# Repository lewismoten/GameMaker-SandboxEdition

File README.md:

# Game-Maker: Sandbox Edition

![Game-Maker: Sandbox Edition. Make 1994 DOS games. No programming. A painted 1994 desk at night by a snowy window: the beige PC shows DOS Game-Maker's Map Maker menu, with a sticky note reading "Too retro? Use today's web" pointing to a tablet showing the site's home page, and around it sit a disk box, TURBO BUTTON magazine, the keyboard, a mug of pencils and the Game-Maker box](docs/social-preview-600x300.png)

Make and play DOS-style games in your web browser, with no programming. A modified fork of
**RSD Game-Maker 3.0**, the 1991–1995 game construction kit by Recreational Software
Designs, whose source Andy Stone released under the MIT License in 2014.

**▶ Play it: https://lewismoten.github.io/GameMaker-SandboxEdition/**

**Videos:** [RSD Game Maker - Sandbox Edition](https://www.youtube.com/watch?v=0riemzdF8gc), a
tour of the web port, the editor and the 1994 desk, and
[More Features](https://www.youtube.com/watch?v=gNEya63wDmo), what has been added since. Both
are in the site's Library too.

This fork is kept by Lewis Moten, who shoveled Fort Ashby's driveways in the winter of 1992
to buy Game-Maker. The desk, the BBSes and _Snowbound_ come from those years: see
[Lewis and Game-Maker](docs/history.md).

## What's in it

- **Three ways to use it** (the Desk, DOS and Web switch at the top right): the _1994 desk_,
  a recreated PC with a DOS prompt, Game-Maker's DOS menus and designers rebuilt from its
  source, a BBS to dial, and the games' boxes, disks and manuals on the shelf; _DOS_, the
  same PC's screen on its own, filling the window without the desk around it; or _today's
  web_ editor with point-and-click editors for every part of a game.
- **Help making good games:** the map editor's Level check plays each scene on the real
  engine, draws a heat map of where the hero got, marks places a player can get stuck and
  offers one-click fixes; the block, monster and sound editors show its findings as badges,
  a Before You Upload checklist ticks itself, and a bot can make a walkthrough of your game.
  The Game-Maker box holds _The Ultimate Owner's Guide_, an advanced booklet on level design,
  tricks from the new games and these tools.
- **A port, not a PC emulator:** Game-Maker and its PLAYGAME player are re-implemented in
  TypeScript from the released C source, and no DOS or x86 code runs. The desk's PC is a
  simulation; some hardware is emulated (VGA mode 13h, the OPL2 FM sound chip).
- **Original file formats:** games are read and written byte for byte as `.GAM`, `.MAP`,
  `.BBL`, `.MON`, `.CHR`, `.CMF`, `.FLI` and the rest, so a game made here still runs in DOS
  Game-Maker and DOSBox, and old games open here unchanged.
- **Byte-identical, checked:** the same code makes the same bytes. `npm run check:games`
  builds each new game twice into separate folders and fails if any file differs;
  `npm run roundtrip` reads every original file, writes it back and compares the bytes;
  `npm run check:same-bytes` hashes every built game file before and after a refactor and
  lists what changed. A refactor must not change a generated byte.
- **The CD's games:** the sample "gameware" (edit a copy) and the shareware (play only,
  with their authors' notices). CD games that shipped without a title demo get one recorded
  for this edition, kept apart from their original files.
- **Fourteen new Sandbox Software games** built for this fork, entirely in code
  ([games/](games)): _Maximus: The Hundred Worlds_, _Sandcastle Knight_, _Snowbound: The $89
  Shovel_, _In The Year 2000!_, _Teddy's Little Big Adventure_, _Teddy's Little Bigger
  Adventure_, _Teddy's Little Biggest Adventure_, _Ohm Sweet Ohm_, _Virus Blaster_, _Final
  Curtain_, _KEEP IT BRIEF! The Tiny Pockets Library_, _Depth Perception_, _Quest for the
  Round Tuit_ and _Tune-Up_. Each comes
  with a manual, box art, printable extras (among them a fold-out World Map and Level Maps)
  and a hidden tin heart, and most hide a felt egg to find.
- **Twelve "bizarre" games**, also built in code from Lewis's own comic songs and
  monologues, dressed as 1995 shareware from The Sofa BBS: eleven by The Bard of Bizarre
  (_Third Goat from the Left_, _Mustard Seed Hustle_, _Thread the Needle, Brother Camel_,
  _Loaf #13_, _Certified Rat Tickler_, _Where's the Remote?!_, _A Fly Named Carl_, _The Great
  Dairy Reckoning of 3:17 A.M._, _Cleanse Me, O Loofah, But Leave My Soul_, _I Screamed, She
  Smirked_ and _Shakespeare in Sweatpants_) and _Veni, Vidi, Risi!_ by Lewis's group of that
  name. They have a Bizarre tab of their own on the home page. Their FM music is arranged
  from the songs' recordings, and they are free to share.
- **The cast** ([#/cast](https://lewismoten.github.io/GameMaker-SandboxEdition/#/cast)):
  the characters who turn up in more than one of the new games, walking on with their own
  game sprites.
- **Demos and walkthroughs:** title demos play with Sound Blaster music, the PC speaker or
  no sound, and every new game has a walkthrough that plays it from power-on to the
  credits on the real engine, with chapters, ready to download as an MP4.
- **The desk PC's utilities:** HEXEDIT, BACKUP, SAVEHACK and GMCRACK, in 1990s dress but
  mainly for looking inside game files, saved games and registration while debugging.
- **The BBSes:** a modem with a line speed to pick (300 baud to unlimited), a tic-tac-toe
  door game played a move a call, and a TTY call to the neighbor in Baudot.
- **Achievements** for what you make, play and find, on the web and in the desk's ACHIEVE.EXE,
  and two score trophies on the desk (best scores and total score) that climb from plastic
  through bronze, silver and gold.
- **The Library** ([#/library](https://lewismoten.github.io/GameMaker-SandboxEdition/#/library)):
  everything to read or print in one place, by game or by kind: each game's manual and box
  paper, its World Map and Level Maps, the Game-Maker box's Owner's Guide, the walkthroughs and
  the videos.
- **Sharing:** export a game as a one-page web game, an installable web app, or a folder
  that runs in DOSBox, or download any game, your own too, as a Mac app, a Windows program
  or a Linux folder that plays offline in its own window (built in the browser; see the
  [Mac](mac/README.md), [Windows](win/README.md) and [Linux](linux/README.md) notes).
  Everything is saved in your browser and works offline.
- **Opening games from other sites:** a link (`?open=<address of the game>`) or a page using
  `window.open` and `postMessage` can open a game here to play or edit, on the desk, in DOS
  Game-Maker or on the web, after the visitor says yes. See
  [Opening games from your site](docs/embed.md).
- **A web player for your old games:** one `.html` file to put on any web host beside your
  Game-Maker game folders. It lists them from an optional `games.json`, starts one from
  `?game=<name>`, and keeps high scores and saved games in the browser, with export and
  import. [Try it with the games here](https://lewismoten.github.io/GameMaker-SandboxEdition/player/)
  or see [The web player](docs/web-player.md).
- **Reusable npm packages:** run Game-Maker DOS files in your own web application with the
  browser engine, build or check game data with the development tools, and load game archives. See
  [npm packages](#npm-packages) for installation and API documentation.

## Screenshots

|                                                                                                                                                                                                                                             |                                                                                                                                                                                                                        |
| ------------------------------------------------------------------------------------------------------------------------------------------------------------------------------------------------------------------------------------------- | ---------------------------------------------------------------------------------------------------------------------------------------------------------------------------------------------------------------------- |
|                                                                                |                                 |
| The home page's Sandbox games                                                                                                                                                                                                               | Editing a copy of Snowbound's LaVale Mall map                                                                                                                                                                          |
|                                                                                             |                                                                             |
| Playing Snowbound                                                                                                                                                                                                                           | The Bizarre games                                                                                                                                                                                                      |
|  |  |
| Game-Maker's DOS menus, rebuilt from its source                                                                                                                                                                                             | Its copy check, with the Owner's Guide beside it                                                                                                                                                                       |

[A tour of the web editor](docs/editor.md) has a picture of each of its editors: maps, blocks,
monsters, the hero, palettes, music, sounds, animations, the Integrator, the Level check and more.

## npm packages

Use these packages in a separate JavaScript or TypeScript project, installed from your
configured npm registry. All include TypeScript declarations.

**[@lewismoten/gamemaker-sandbox-engine](web/packages/engine/README.md)** runs games from
their original DOS files in a browser and includes the audio worklet. Its README provides
the API, a complete player example, and instructions for supplying game files.

```sh
npm install @lewismoten/gamemaker-sandbox-engine
```

**[@lewismoten/gamemaker-sandbox-tools](web/packages/tools/README.md)** provides development
APIs for reading and writing game formats, drawing indexed artwork and text, building
palettes and audio, and running headless checks. Its README documents the APIs and examples.
Use Node.js 22.12 or newer for these tools.

```sh
npm install --save-dev @lewismoten/gamemaker-sandbox-tools
```

The tools run during development; browser playback uses the engine and generated game data.

**[@lewismoten/gamemaker-sandbox-archives](web/packages/archives/README.md)** discovers games
in folders, ZIPs, nested archives, and ZIP-based self-extracting executables. It can also
create ZIPs for single-file downloads. Its README covers extraction, game selection, and
passing the unpacked file entries to the browser engine.

```sh
npm install @lewismoten/gamemaker-sandbox-archives
```

## Run it yourself

You need [Node.js](https://nodejs.org/) 22.12 or later.

```sh
npm ci             # from the repository root; builds workspace packages and game output
npm run dev        # http://localhost:5173
npm run dev -- -- --port 4174  # use another port; the second -- forwards flags to Vite
npm test           # the test suite (vitest)
npm run typecheck  # tsc --noEmit
npm run build      # refresh game output, typecheck, then the static site in web/dist
npm run format     # Prettier (config at the repo root)
npm run lint       # ESLint
npm run verify:changed  # quick pre-merge check of only what your branch touched (vs origin/develop; --base <ref>)
npm run verify     # the full check: format, lint, typecheck, every test, packages, release notes
```

This is an npm workspace monorepo with one root lockfile. The root `package.json` exists to declare
the workspaces (`web` and `web/packages/*`) so a single `npm ci` links them and one
`package-lock.json` pins everything; `npm start` there runs the web dev server. The app is in `web/`;
self-contained engine, archives and tools packages own their source in `web/packages/`.
See [workspace development](docs/monorepo.md) for package ownership, isolated builds and release checks.

The repository was reformatted with Prettier in a few big commits. They are listed in
[`.git-blame-ignore-revs`](.git-blame-ignore-revs), which GitHub's blame view already skips.
To make `git blame` on your own computer skip them too, run this once in your clone:

```sh
git config blame.ignoreRevsFile .git-blame-ignore-revs
```

The new games are rebuilt from their code, also from `web/`:

```sh
npx vite-node ../games/teddy/build.ts             # rebuild games/teddy/disk
npx vite-node ../games/teddy/tools/check.ts       # play-test it headlessly
npx vite-node scripts/macDmg.ts teddy             # a Mac .dmg of it, in ../dist/mac
npx vite-node scripts/winExe.ts teddy             # a Windows .exe, in ../dist/win
npx vite-node scripts/linuxTar.ts teddy           # a Linux .tar.gz, in ../dist/linux
```

To check every game at once (each one rebuilt and compared with its committed disk, played
by its bot, its walkthrough replayed, its text, hidden items and levels checked), run
`npm run check:games` from `web/`. It prints a table and fails on any regression; add
`-- --game teddy` for one game or `-- --quick` to skip the rebuild compare.

The site is served by GitHub Pages from the `gh-pages` branch: one commit holding the built site of a
`pages-v*` release tag, made on the maintainer's computer by `npm run release:pages` (see
[package releases](docs/package-releases.md#publishing-the-site-gh-pages)). Branch pushes do not publish the site.
The `mac-dmg`, `win-exe` and
`linux-tar` workflows build every game for each system and attach them to a GitHub release.
Engine, tool, and archive releases are described in [Package releases](docs/package-releases.md).
Games are deployed as standalone DOS ZIPs with [permanent download links](docs/game-distributions.md),
shared by the browser player, editor and DOS downloads.
Every GitHub job stops after five minutes, including deployments and release builds.
Checking every game takes far longer than that, so run `npm run check:games` (with the rebuild
compare, about 20 minutes) yourself before committing a game.
Run whole-game checks locally with `npm run check:games` from `web/` (or add
`-- --game <id>` for one game). GitHub jobs are capped at five minutes; tests over
50 ms and isolated package-consumer checks run locally.

## Where things are

| Folder                                          | What it holds                                                                                                                                                                                                                                                                                                                                                                                                                                       |
| ----------------------------------------------- | --------------------------------------------------------------------------------------------------------------------------------------------------------------------------------------------------------------------------------------------------------------------------------------------------------------------------------------------------------------------------------------------------------------------------------------------------- |
| [`web/`](web)                                   | The browser app. [web/README.md](web/README.md) explains it; [web/src/README.md](web/src/README.md) maps the source.                                                                                                                                                                                                                                                                                                                                |
| [`games/`](games)                               | The Sandbox Software and Bard of Bizarre games, built in code, and the shared kit that builds and play-tests them. See [games/README.md](games/README.md) and [games/kit/README.md](games/kit/README.md).                                                                                                                                                                                                                                           |
| [`docs/`](docs)                                 | [A tour of the web editor](docs/editor.md); for site owners, [opening a game from your own site](docs/embed.md) and [the web player](docs/web-player.md); and [Lewis and Game-Maker](docs/history.md), how the project came about; [how I built this](docs/agents/how-i-built-this.md) and [working with AI coding agents](docs/agents/README.md), what building it that way taught; and [case studies](docs/research/README.md) of measured fixes. |
| [`mac/`](mac), [`win/`](win), [`linux/`](linux) | The small native players that a downloaded game runs in, and how they are built. See [mac/README.md](mac/README.md), [win/README.md](win/README.md) and [linux/README.md](linux/README.md).                                                                                                                                                                                                                                                         |
| `cd/`                                           | The original Game-Maker CD image, with its sample and shareware games.                                                                                                                                                                                                                                                                                                                                                                              |
| [`code/`](code)                                 | The original DOS C/C++ source. See [code/README.md](code/README.md).                                                                                                                                                                                                                                                                                                                                                                                |
| `runtime/`                                      | A DOS `C:` drive with Game-Maker installed, for DOSBox.                                                                                                                                                                                                                                                                                                                                                                                             |

## The original DOS version

To run the original Game-Maker, install [DOSBox](https://www.dosbox.com/), start it from
the root of this repository, and type:

```
mount c runtime
c:
cd \run\gm
gm
```

To build the DOS source you also need the Borland C++ compiler, which this fork doesn't
include, nor the Borland and Creative library files it links (none are covered by the
MIT License; NOTICE.md lists them). Copy the `tools/` folder and those files from the
[original 2014 repository](https://github.com/gandrewstone/GameMaker) into this one, then,
following Andy Stone's original notes, in DOSBox:

```
c:
dev.bat          (mounts the compiler as T: and the source as D:)
d:
cd gm
del *.obj
del *.exe
creatall         (or "create palchos", "create blocedit"… for one program)
```

## Learn more

- [CONTRIBUTING.md](CONTRIBUTING.md): branches, checks, release notes and credits
- [Game-Maker on Wikipedia](https://en.wikipedia.org/wiki/Game-Maker)
- ["RSD GameMaker"](https://effluviaofascatteredmind.blogspot.com/2011/06/rsd-gamemaker.html),
  Andy Stone looking back on it in 2011: building it as a teenager with his family, and
  leaving every game open in the editors so players could learn from and remix each other's work
- [The Game-Maker wiki (archived)](https://web.archive.org/web/20260807223841/https://aderack.com/game-maker/index.php?title=Main_Page)
- [The original 2014 source release](https://github.com/gandrewstone/GameMaker)

## Credits and license

RSD Game-Maker was created by G. Andrew Stone, G. Oliver Stone, Oliver Stone Jr. and Joan
Stone. This fork is by Lewis Moten; the web port was written with Claude Opus 5.5, with AI
assistance doing most of the porting and code generation. The Bard of Bizarre songs'
lyrics were shaped with ChatGPT from Lewis's prompts and their music made with Riffusion
(now Google Flow Music). The CD's games belong to their authors, as shareware or samples distributed on the RSD CD, and are not covered by the MIT License; neither are games you import. See [NOTICE.md](NOTICE.md)
for full credits, the story behind this fork and third-party trademarks.

Released under the [MIT License](LICENSE). It covers the original source Andy Stone released and this fork's own code and content; third-party material and other authors' games keep their own terms (NOTICE.md lists them).

The [native SDL host prototype](hardware/pi-player/README.md) compiles the [Pocket Player](https://github.com/lewismoten/gamemaker-pocket) core (its own repository) for macOS and prepares the Raspberry Pi OS Lite player.

The [courier C99 wire library](hardware/courier/README.md) provides self-checking courier IDs and the capsule v1 codec for hardware integrations.

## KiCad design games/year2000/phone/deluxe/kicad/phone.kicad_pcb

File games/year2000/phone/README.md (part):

# THE PHONE OF THE FUTURE (electronics, rev C)

A solderable toy kit that goes with In The Year 2000!: "a real working wireless phone", the way a 1993 game
imagined one. Infrared voice and touch tones, an eight-digit red display, a real pulse dial, a PIC16F628A and a
CM8870-family tone decoder, through-hole parts only. Two phones are needed to play: digits dialed on one appear on any
phone in sight (no call set-up).

**This is an untested design. Nobody has built one. Treat every claim below as "should", not "does".**
The schematic and board pass KiCad's electrical and design-rule checks and the firmware's logic passes a simulator
I wrote; nothing was powered, soldered or listened to.

Rev C is the cheap, easy-to-build revision. Rev B cost about $68 a phone in parts (most of it a $24 display driver), needed a
72 x 172 mm board (about $96 for three from OSH Park) and a programmer that may not support its chip. Rev C is about $17 a phone in
parts, a 99 x 99 mm board in the cheapest tier at JLCPCB and PCBWay, and a programmer built from an Arduino Nano. The numbers and
sources are in the cost sheet (`.for-lewis/research/phone-of-the-future-parts.md`, not in the repository); the short version is
in "What Rev C changed" below.

## Two builds, named the way Dex would

Dex Dynamo (age 11) wrote a twenty-page science fair report, THE POCKET TELEPHONE, and Sparky 3000 ate it. This kit is
what he would build from it, in two sizes. Both names are on the silkscreen (front and back) and in the desk's 3D viewer.

|       | **Science Project No. 2: The Pocket Telephone, Junior Lab Edition (parts from any hobby shop)**                                                                 | **Science Project No. 1: The Pocket Telephone (Deluxe Model)**                                                |
| ----- | --------------------------------------------------------------------------------------------------------------------------------------------------------------- | ------------------------------------------------------------------------------------------------------------- |
| Where | this folder                                                                                                                                                     | `deluxe/` (the earlier Rev C: sources restored from commit `7e8548a11`, see `deluxe/README-earlier-rev-c.md`) |
| Board | 99 x 99 mm, the cheapest board tier                                                                                                                             | 73.66 x 175.26 mm                                                                                             |
| Parts | PIC16F628A, clone MAX7219, 6 mm tactile switches, ZEPPP programmer; the battery holder and the microphone capsule are off the board, in the shell's battery bay | the long board; the 4 x AAA holder and the microphone are in the bay                                          |
| Shell | one full-width case: earpiece pod, front cover, back tray with the battery bay behind the dial module, battery door, six screws                                 | front cover, back tray with the bay (battery door in its floor)                                               |

Each folder rebuilds on its own (`deluxe/tools/` has its own generators and shares `tools/silkart.py` and `tools/dex_art.py`).
The rest of this file describes the Junior Lab Edition; the Deluxe Model differs in its board and its on-board battery holder.

## The 3D-printed shell and the dial module

`tools/shell.ts` builds each variant's shell as distance fields with the repository's trinket tools (`web/packages/tools/src/mesh/`), sized from its own
`mechanical/interface.json`, `kicad/qr_spots.json` and `viewer/parts.json`. It writes one binary STL per printed part, in printing orientation, to
`<variant>/shell/`, checks each (size, triangles, pieces, thin specks, overhang) and merges every part into `viewer/parts.json` + `parts.bin`, in the
groups `shell`, `dial` and `battery`, so the desk's viewer explodes the case around the board. The Junior Lab case is `tools/shellCheap.ts` (with the dial in
`tools/dialModule.ts`); the Deluxe keeps its own shell in `tools/shellParts.ts`, which is described in `deluxe/README-earlier-rev-c.md`.

### The Junior Lab case: one full-width body

The case is 103.8 mm wide from the top to the chin (the board is 99 x 99) and about 240 mm long, 34 mm thick. Seen from the front, top to bottom:

1. **Earpiece pod** (above the board, between the two infrared parts): the 28 mm speaker clips under the cover's roof, behind a grille of 2 mm holes. Two
   2 mm arms per clip follow the speaker's rim and end in a barb (an 0.8 mm ledge under its back rim), so the speaker snaps in from the back and nothing is glued.
   Two wires (+ is the square pad) run from the board's LS1 pads. This frees the 28 mm circle the speaker used on the board (616 mm2; the pads stay).
2. **The 99 x 99 board**, clamped between the cover's and the tray's walls by the corner bosses.
3. **Lower body**: the dial module sits in the cover (its plate stands 0.8 mm proud of the face), the 4 x AAA holder lies behind it in the tray (the module's base
   lies 0.2 mm over the holder like a lid), the microphone capsule is at the chin under a grille.

_Why this layout._ The dial is below the board where a thumb or finger reaches it best, with room for a 74 mm plate and 13 mm holes. The heaviest part, the
battery, is directly behind the dial, so the phone's weight sits in the palm of the hand that holds the lower body, the thumb reaches the TALK and CLEAR caps
on the board's lower edge, the earpiece is at the top and the mouthpiece at the bottom, 190 mm apart, about a real handset's span. The back is flat and closed.

- **Front cover**: covers everything except the dial opening (a 76.4 mm hole), the display window, the speaker and mouthpiece grilles and the TALK / CLEAR
  caps. The dial module's tube hangs from the roof around the opening; the base's rim seats against its end, so nothing is glued. The finger stop's clip
  comes through a small slot at 4 o'clock. It prints face down.
- **Back tray**: closed, one flat floor 20.7 mm under the board's back plane (a stepped floor would print as an 11,000 mm2 overhang). The battery cradle has crush
  ribs 0.3 mm off the holder on all four sides; the door is in the floor under the holder, so the cells change **without opening the case**. The volume wheel's
  slot is in the side wall. Six screw seats.
- **Six screws, all from the back.** M3 x 30 pan-head **thread-forming (self-tapping) screws**, heads on the back, into 2.5 mm pilot holes in six bosses of the
  front cover: the case's two top corners (they pass through the board's top mounting holes and clamp it), the board's two lower mounting holes (the
  board is clamped between bosses in both halves), and the two corners of the chin. The cover and tray have no other screw bosses. The dial uses the same kind
  of screw (M3 x 10, into a 2.5 mm pilot in its post). Why not heat-set inserts: a lead stub of a part on the back stands 3.4 mm from the board's top left hole, which
  leaves a boss only 2.4 mm in radius, too small for an insert. The pilot holes stop short of the roof (nothing shows on the face).
- **Battery holder**: held by the tray's cradle (ribs on all four sides, 0.3 mm of slack), crush ribs, and the module's base 0.2 mm over its top. Most 4 x AAA
  holders have a screw hole in the middle, but the part listed here (Parts Express 142-254) is not checked for one, so no screw is used. If yours has a center
  hole, a screw from the back into a boss would be an upgrade.
- **Microphone**: the 9.7 mm capsule in a collar hanging from the cover, at the chin. Its twisted pair runs from the board's MK1 pads, out to the corridor
  beside the holder (x 2.5 and 4.5 mm), down the lower body and across below the dial's base to the capsule.
- **Wires to the dial's switches**: SW2 and SW3 are 6 mm tactile switches in the dial module, with two thin wires each to wire pads at the bottom of the board's old
  dial circle (24, 80 and 36, 80 mm). The wires run along the front of the board's left side, in the cover's cavity, to the module. (Their path is not drawn.)

### The dial module

A self-contained stack, drawn from scratch (no mesh or STL copied) in `tools/dialModule.ts`, numbers shared with the mechanism check in `tools/dialParams.json`.
Front to back: **plate**, **cam wheel**, **spring**, **base**. Fat-finger sizing: 13 mm finger holes on a 29 mm ring (webs of 2.0 mm), a 74 mm plate, a clip-on
finger stop with an arm over the holes at 4 o'clock, hole 1 at 3 o'clock, 30 degrees from the stop.

| Part           | What it is                                                                                                                                                                                                                                                          |
| -------------- | ------------------------------------------------------------------------------------------------------------------------------------------------------------------------------------------------------------------------------------------------------------------- |
| `dial-plate`   | 74 mm plate, ten 13 mm holes, a hub tube with two drive tabs, two flexure pawls (2 mm thick, 18 mm of arm), a 1.5 mm wall under the rim that presses SW3 whenever the plate is off rest, a rest dog                                                                 |
| `dial-cam`     | the pulse cam wheel: an internal 12-tooth ratchet the pawls drive only on the return, 12 lobes on its rim that press SW2 sideways, 12 detent teeth, a smooth band for the brake, a grease groove under its web                                                      |
| `dial-spring`  | the printed flat spiral spring in one piece with its own frame ring (the frame has three lugs that key into a wall on the base, six slots in the hub ring set the preload)                                                                                          |
| `dial-base`    | the backplate: the center post with a 2.5 mm screw pilot, the **ten digit pedestals** (the digits are engraved on them, 2.6 mm under the plate, so they read through the holes), switch cradles, the hold-back and brake leaves, the rest post, an ear for the clip |
| `dial-stop`    | the finger stop: a C-clip over the base's ear, a post through the cover's slot, an arm over the plate; printed on its side                                                                                                                                          |
| `dial-bushing` | the spacer the washer clamps, so the plate turns freely on the post and cannot lift off (the washer overlaps the plate's hub lip by 1.2 mm each side)                                                                                                               |
| bought         | 2 tactile switches (SW2, SW3, on the BOM already), an M3 x 10 thread-forming screw, an M3 fender washer 9 mm outside diameter                                                                                                                                       |

- **One-way counting (the ratchet clutch).** The plate winds clockwise. Two flexure pawls on the plate ride over a 12-tooth ratchet on the cam wheel, one click
  every 30 degrees, and a hold-back leaf on the base keeps the cam wheel still, so SW2 does nothing on the wind. On the return the pawls catch the teeth's steep
  faces and carry the cam wheel back with the plate, and the 12 lobes press SW2 once per 30 degrees of cam travel. Hole 1 is one pitch (30 degrees) from the
  stop, so digit n travels 30 x n degrees and gives exactly n pulses (0 is 300 degrees, 10 pulses). When the plate stops at rest, the hold-back leaf's gentle
  forward flank lets the cam coast the last 8 degrees to its parked tooth, which also puts every ridge 8 degrees ahead of the pawl, so a finger that winds up to
  21 degrees past the stop (or 0.5 degrees short) still crosses the same number of ridges. `shell.ts` runs the **angle walk** (`tools/dialMechanism.ts`, the
  same arithmetic as the Stage Box's mechanism check) for every digit and fails the build if a wind gives a pulse or a return gives other than n; the phone's
  firmware simulator (`tools/picsim.py`) plays the same walk into the real hex, with contact bounce.
- **Retention.** The post stands on the base; the M3 x 10 screw goes through the washer and the bushing into the post's pilot and clamps only the bushing. The plate
  turns on the post and its hub lip sits between the bushing's flange-free top and the washer, so it can lift only 0.6 mm and never fall out. No snap prongs.
- **Return spring.** First choice, the printed spiral: strip 1.6 x 3.0 mm, pitch 2.8, 4 turns (about 300 mm), parameters in `DM.spring`. In PETG (E about 2 GPa,
  an assumption) it gives about 5 N mm at rest (60 degrees of preload) and 30 N mm fully wound (about 1 N at a finger), strain 1.3 % (PETG takes about 2 %, PLA
  about 1 %, and PLA creeps: use PETG). Fallback: a metal torsion spring, 0.5 mm wire, 13 mm coil, fits around the spring frame's hub ring (OD 16 mm; the printed
  spiral is snipped off) with one leg in a hub slot and the other in a lug notch of the base's wall.
- **Speed.** A free printed dial returns in about 50 ms, far too fast; the cam wheel is slowed by the grease film between its web and the spring (a 0.4 mm gap, a
  groove to hold the grease) and by the brake leaf's friction. `shell.ts` prints an estimate for several greases; the first print decides (thin the grease or add a
  shim to change the film). The firmware accepts 8 to 15 pulses a second.
- **Credit.** Inspired by "Rotary Dial mechanism" by dAcid (Thingiverse 3153349, CC BY 4.0, https://www.thingiverse.com/thing:3153349). Ideas taken from it: a printed
  spiral spring in one piece with a frame, a clip-on finger stop, a headed center screw through a stack that prints flat, and digits printed under the holes. This
  dial differs: a ratchet clutch so that only the return counts (that dial reads both ways with an optical sensor and software), tactile switches in place of the
  optical slotted disc, a bigger plate with 13 mm holes, a separate cam wheel, a grease damper, a heat-free self-tapping screw, and every dimension is new
  (no STL, mesh or spring parameter was copied or adapted, so NOTICE.md has no entry for it).

### Assemble the module and the case

Print the plate, cam wheel, spring, base and the clip in **PETG** (the flexure pawls, leaves and the spiral spring crack and creep in PLA); the cover, tray, caps and door can be PLA.
The STLs in `shell/` are in printing orientation.

1. **Dial module (on the bench).** Press SW3 flat into its low frame on the base (pins down through the four holes) and SW2 on its side into its cradle, button toward the center. Solder
   two wires to each switch (pulse and ground; about 100 mm). Set the spring plate on the base, its three lugs in the wall's notches. Put the cam wheel over it
   (a dab of grease on the spring plate's top and in the cam's groove). Wind the plate 60 degrees clockwise from rest and lower it on the cam wheel: the hub tube's two tabs go into two
   opposite slots of the spring's hub ring, the pawls fall into the cam's teeth. Let it back to its rest dog. Drop the bushing on the post, then the washer, then the M3 x 10 screw: snug, then back off an eighth of a turn
   so the plate turns freely. Press the clip over the base's ear.
2. **Check the dial** before the case: wind a digit to the clip's arm and let go; SW3 should close at once and SW2 should click open and shut once per 30 degrees of the return (with a meter, or the board).
3. **Case.** Cover face down: the speaker (two wires) pops into the pod's clips from behind; the microphone capsule goes in its collar; the caps drop into their holes. Lay the dial module in the
   tube from behind (the plate through the opening, the clip's post through its slot). Lower the board onto the cover's bosses, solder the dial and speaker wires to their pads, the holder's leads and
   the microphone's pair, set the holder in the tray's cradle and the tray on the cover. Six M3 x 30 screws from the back, then the battery cells and the door.

### Lead and solder clearance

Every pad is a plated through-hole, so a part on one face has its trimmed lead and solder fillet standing out of the other. The viewer's models leave them out,
so `tools/clearance.ts` adds them (a 0.9 mm radius fillet 1 mm tall, then a 0.3 mm wire, to **LEAD = 2.5 mm** from the board face, at every pad of
`kicad/placement.json`) and measures every printed part (including the whole dial module and the six screw bosses) against those stubs and against every part
body. `shell.ts` fails the build, and `web/src/desk/boxes/phone/phoneClearance.test.ts` fails the tests, if any gap is under 1 mm; the numbers go to
`viewer/clearance.json`. The 2.5 mm is an **assumption** (IPC-A-610 allows 0.5 to 1.5 mm; a hobbyist trims to about 1 to 2 mm). The dial module is below the board, so
it is far from every stub; the closest approaches are the screw bosses and the cover over the board.

Nothing was printed. The fits (0.3 mm), the lobes' travel (0.15 mm of overtravel), the spring and the grease are starting guesses.

## What is printed on the board

Front: the project name ("SCIENCE PROJECT NO. 2" and "JUNIOR LAB EDITION", or "NO. 1" and "DELUXE MODEL"), "IN THE YEAR 2000!", "SANDBOX SOFTWARE" and
"MADE WITH GAME-MAKER". The front of the 99 x 99 board is full of through-hole pads, and the dial and speaker cover their circles, so there is no
room there for a code. On the back, in the blank spots: two QR codes (the game's site, and this folder's parts list and build steps on GitHub) and a
block-art picture of Dex (`tools/dex_art.py`, from his sprite, as big as the back's pads leave room for: 16.8 x 18.9 mm on the Junior Lab board, with the few pixels that would land on a pad left out like the front's art clipped away from pads): one color of silkscreen, with tone shown by diagonal hatching and cross-hatching and his
face and hands left bare, so he is never an undressed outline. A code is silkscreen where a module is light and bare soldermask where it is dark.
`tools/silkart.py` draws them (QR from OpenCV's encoder, Apache-2.0). Modules are 0.5 mm, except the parts code on the Junior Lab board (0.44 mm) and the
site code on the Deluxe board (0.45 mm), which had to be a little smaller to fit. `tools/qrscan.py` decodes the rendered preview and compares it with the URL:
the layout scans; whether a phone camera reads these small modules from a real board has not been tried.

## Rebuild everything

From the repository root, one command rebuilds both variants (schematic, board, ERC and DRC, Gerbers, 3D parts file, BOM, previews, QR scan, shell)
and writes `games/year2000/phone/out/build.log`:

```sh
npm run phone:build
```

## What is here

| Path                                                | What it is                                                                                                         |
| --------------------------------------------------- | ------------------------------------------------------------------------------------------------------------------ |
| `kicad/phone.kicad_sch`, `phone.kicad_pcb`          | The KiCad 9 project (written by the scripts below; open it in KiCad to look or edit)                               |
| `kicad/phone.pretty/`, `phone.kicad_sym`, `models/` | Big-pad footprints, the two local symbols (CM8870, 4-digit display), and the simple 3D models (`.wrl` and `.step`) |
| `firmware/phone.asm`                                | PIC16F628A firmware, gpasm                                                                                         |
| `bom.csv`, `PARTS.md`                               | Bill of materials and readable parts list (`tools/bom.py`)                                                         |
| `mechanical/interface.json`                         | Board outline, holes, where everything sits and how tall (for the shell)                                           |
| `viewer/parts.json`, `parts.bin`                    | The board and every part as a compact triangle set for the site's 3D viewer (`tools/export3d.sh`)                  |
| `tools/`                                            | Generators and checks (below)                                                                                      |
| `out/` (git-ignored)                                | Gerber zip, schematic PDF, ERC and DRC reports, the `.hex`, the GLB files and the preview PNGs                     |

The KiCad files and `viewer/` are committed on purpose: they are the design, and the site's GitHub build has no KiCad.
Change `tools/design.py` (circuit) or `tools/gen_pcb.py` (placement, art) and re-run rather than hand-editing, unless you
take the project over in KiCad from here on.

## Commands (from `games/year2000/phone/`)

```sh
python3 tools/gen_sch.py && python3 tools/gen_pcb.py   # rewrite the schematic and board (routing takes a few minutes)
tools/export.sh          # sexp check, ERC, DRC, gerbers/ (tracked), out/phone-gerbers.zip, out/phone-schematic.pdf
tools/export3d.sh        # out/phone.glb, out/phone-bare.glb, out/front.png, out/back.png, then viewer/parts.json + parts.bin
tools/build_firmware.sh  # gpasm -> firmware/phone.hex (tracked, both builds), then the simulator checks
python3 tools/bom.py && python3 tools/mech.py
```

Needs KiCad 9 (`kicad-cli`; set `KICAD_CLI` if it is not in `/Applications`), `gputils` (`brew install gputils`) and
Python 3. The scripts never use KiCad's own Python: `tools/sexp_check.py` validates a file before any KiCad tool opens it.
To regenerate the viewer file after a board change run `tools/export3d.sh` and commit `viewer/`. Its format is described
at the top of `tools/glb_tool.py`. `tools/glb_check.py` checks that every part's mesh sits on the right side, over its footprint.

## What Rev C changed (and why)

Prices are quantity 1, checked 2026-11-03 (sources and caveats are in the cost sheet).

| Decision                     | Rev B                                                | Rev C                                                                                                          | Saves per phone     |
| ---------------------------- | ---------------------------------------------------- | -------------------------------------------------------------------------------------------------------------- | ------------------- |
| Display driver               | MAX7219CNG+ $23.97                                   | clone MAX7219N (HGSEMI, DIP-24, LCSC) about $1; genuine MAX7219CNG is $7.95 at Jameco if a clone is not wanted | $22.97 (or $16.02)  |
| Microcontroller              | PIC16F84A $4.95, 12 to 13 V programming              | PIC16F628A $2.20, same 18-pin DIP and pinout, programmable at 5 V                                              | $2.75               |
| Programmer (once)            | PICkit 5 $79.68, F84A support unconfirmed            | Arduino Nano clone about $9 and the open-source ZEPPP sketch                                                   | $70 once            |
| Board                        | 72 x 172 mm, about $96 for 3 (OSH Park)              | 99 x 99 mm, $2 for 5 (JLCPCB) or $5 for 10 (PCBWay), plus shipping                                             | about $75 per order |
| Regulator                    | LM2940T-5.0 $2.22, TO-220                            | MCP1702-5002E/TO $0.65, TO-92                                                                                  | $1.57               |
| Dial switches                | two lever microswitches $5.22                        | two 6 mm tactile switches $0.50 (the dial's cams press them from above)                                        | $4.72               |
| Battery and power switch     | 4 x AAA holder $2.54 and slide switch $0.95          | one holder with cover and switch, $1.93                                                                        | $1.56               |
| Sockets                      | four machined sockets $5.48                          | two stamped 18-pin sockets $0.16 (the PIC and the decoder)                                                     | $5.32               |
| IR photodiode and LED        | BPW34 $1.82, TSAL6200 $0.50                          | 5 mm IR photodiode $0.25, 5 mm IR LED $0.16                                                                    | $1.91               |
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
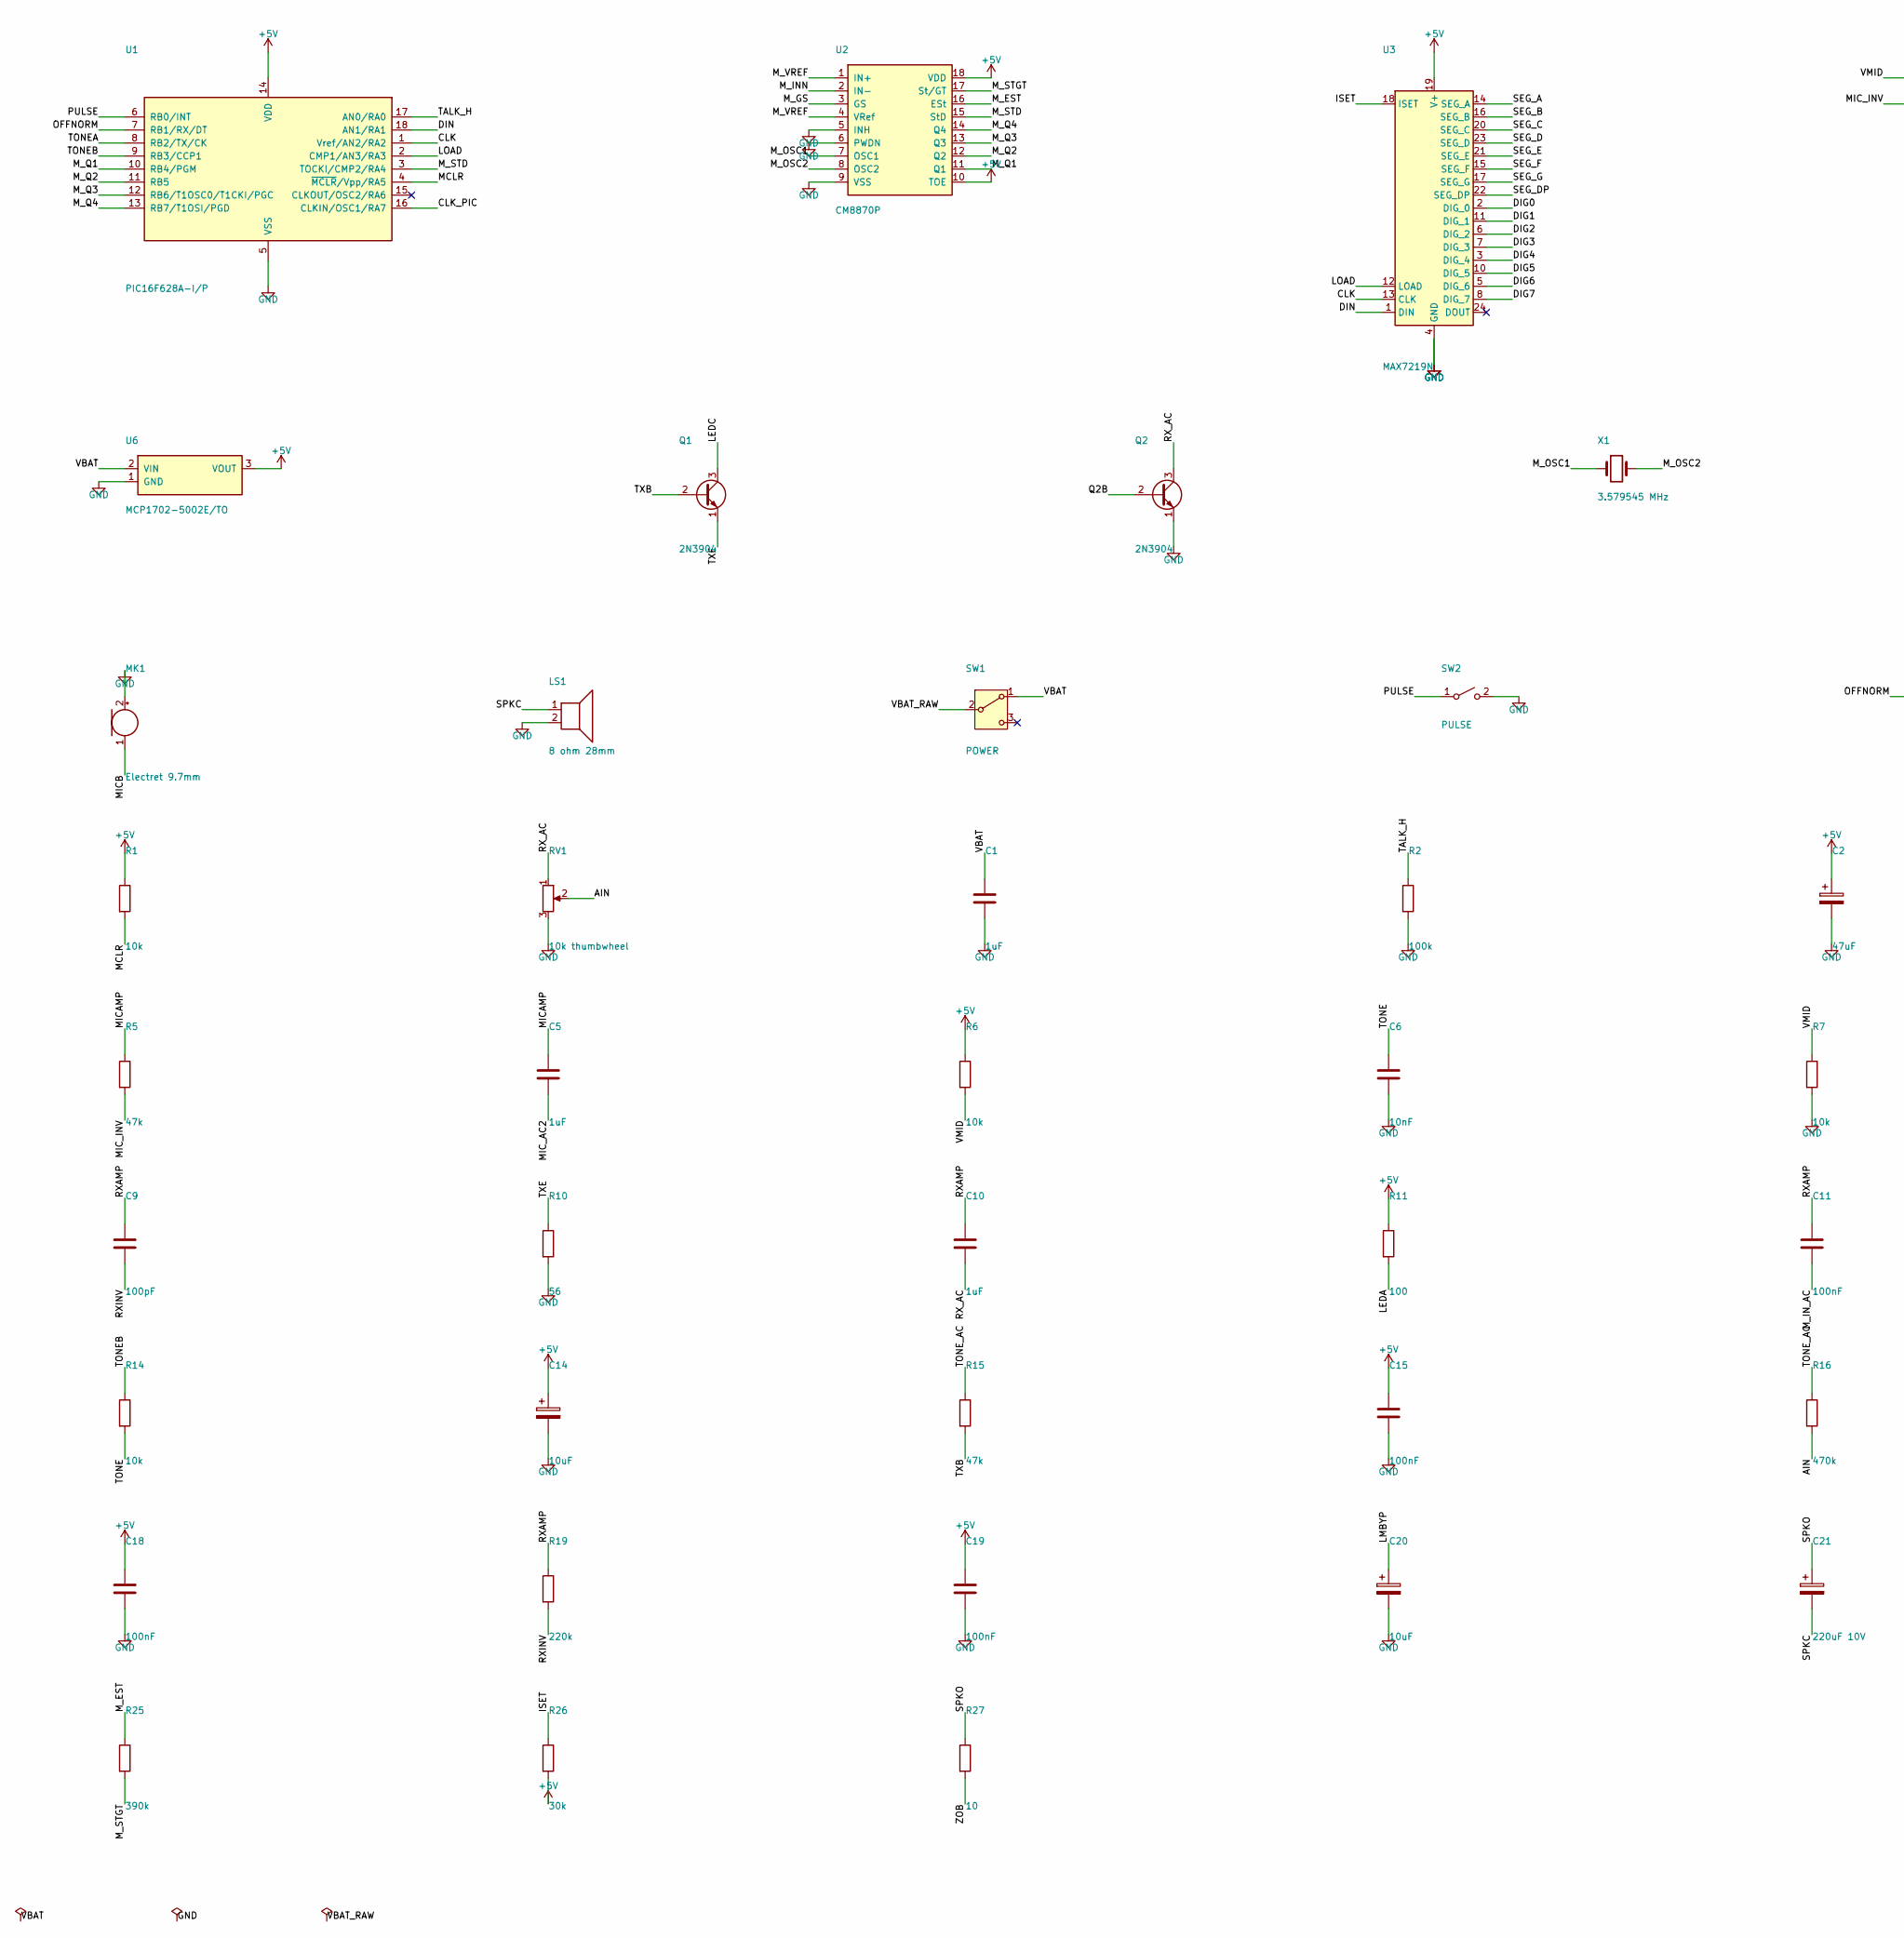
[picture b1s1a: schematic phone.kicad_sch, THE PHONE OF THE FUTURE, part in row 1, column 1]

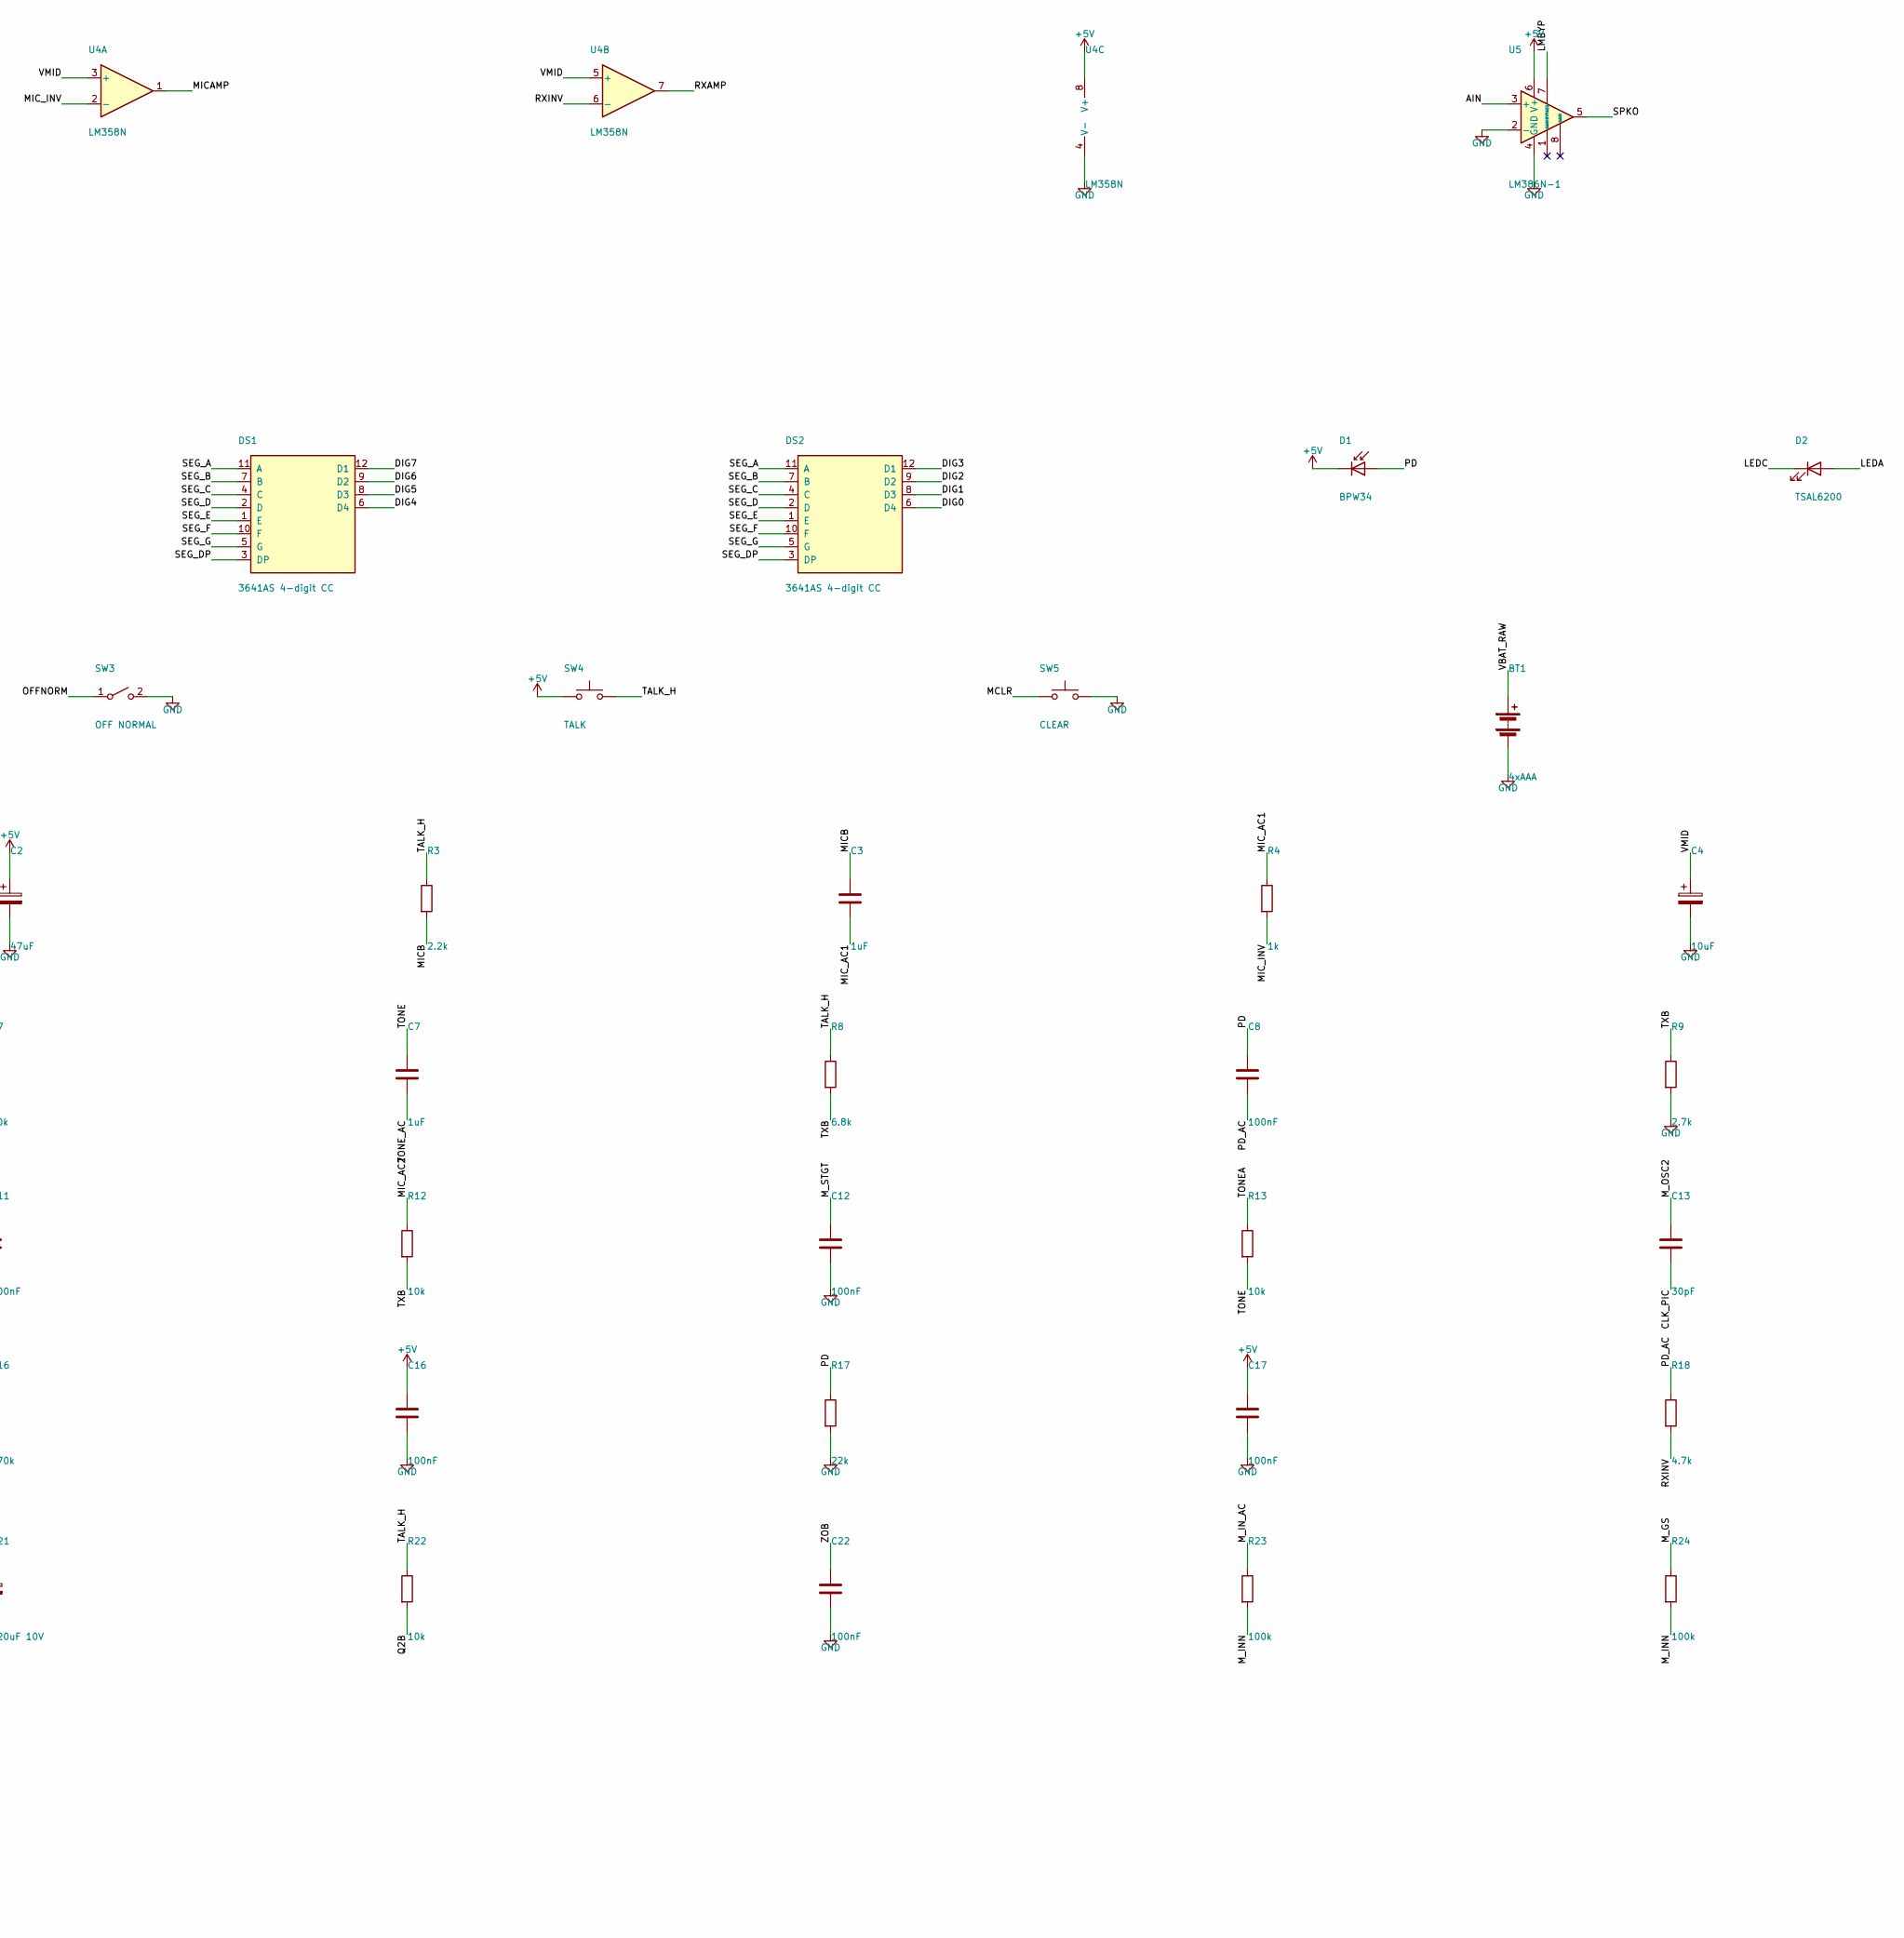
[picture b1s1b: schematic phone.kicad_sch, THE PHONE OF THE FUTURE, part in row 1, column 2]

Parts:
BT1: 4xAAA; BatteryLeads_2pad_BigPads
C1, C3, C5, C7, C10: 1uF; C_Disc_P5.08mm_BigPads
C2: 47uF; C_Radial_P2.54mm_BigPads
C4, C14, C20: 10uF; C_Radial_P2.54mm_BigPads
C6: 10nF; C_Disc_P5.08mm_BigPads
C8, C11, C12, C15, C16, C17, C18, C19, C22: 100nF; C_Disc_P5.08mm_BigPads
C9: 100pF; C_Disc_P5.08mm_BigPads
C13: 30pF; C_Disc_P5.08mm_BigPads
C21: 220uF 10V; C_Radial_P2.54mm_BigPads
D1: BPW34; Photodiode_BPW34_BigPads
D2: TSAL6200; LED_5mm_BigPads
DS1, DS2: 3641AS 4-digit CC; DISP4_CC_0.36in_12pin
LS1: 8 ohm 28mm; Speaker_28mm_BigPads
MK1: Electret 9.7mm; Mic_Electret_2pad_BigPads
Q1, Q2: 2N3904; TO-92_Inline_BigPads
R1, R6, R7, R12, R13, R14, R22: 10k; R_Axial_P5.08mm_BigPads
R2, R23, R24: 100k; R_Axial_P5.08mm_BigPads
R3: 2.2k; R_Axial_P5.08mm_BigPads
R4: 1k; R_Axial_P5.08mm_BigPads
R5, R15: 47k; R_Axial_P5.08mm_BigPads
R8: 6.8k; R_Axial_P5.08mm_BigPads
R9: 2.7k; R_Axial_P5.08mm_BigPads
R10: 56; R_Axial_P5.08mm_BigPads
R11: 100; R_Axial_P5.08mm_BigPads
R16: 470k; R_Axial_P5.08mm_BigPads
R17: 22k; R_Axial_P5.08mm_BigPads
R18: 4.7k; R_Axial_P5.08mm_BigPads
R19: 220k; R_Axial_P5.08mm_BigPads
R25: 390k; R_Axial_P5.08mm_BigPads
R26: 30k; R_Axial_P5.08mm_BigPads
R27: 10; R_Axial_P5.08mm_BigPads
RV1: 10k thumbwheel; Thumbwheel_10k_3pin_BigPads
SW1: POWER; SW_Slide_SPDT_BigPads
SW2: PULSE; Microswitch_Lever_BigPads
SW3: OFF NORMAL; Microswitch_Lever_BigPads
SW4: TALK; SW_Tactile_6mm_BigPads
SW5: CLEAR; SW_Tactile_6mm_BigPads
U1: PIC16F628A-I/P; DIP-18_W7.62mm_BigPads
U2: CM8870P; DIP-18_W7.62mm_BigPads
U3: MAX7219N; DIP-24_W7.62mm_BigPads
U4: LM358N; DIP-8_W7.62mm_BigPads
U5: LM386N-1; DIP-8_W7.62mm_BigPads
U6: MCP1702-5002E/TO; TO-92_Regulator_BigPads
X1: 3.579545 MHz; Crystal_HC49_BigPads

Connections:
+5V: C2.1, C14.1, C15.1, C16.1, C17.1, C18.1, C19.1, D1.1 (K), R1.1, R6.1, R11.1, R26.2, SW4.1, U1.14 (VDD), U2.10 (TOE), U2.18 (VDD), U3.19 (V+), U4.8 (V+), U5.6 (V+), U6.3 (VOUT)
AIN: R16.2, RV1.2, U5.3 (+)
CLK: U1.1 (Vref/AN2/RA2), U3.13 (CLK)
CLK_PIC: C13.2, U1.16 (CLKIN/OSC1/RA7)
DIG0: DS2.6 (D4), U3.2 (DIG_0)
DIG1: DS2.8 (D3), U3.11 (DIG_1)
DIG2: DS2.9 (D2), U3.6 (DIG_2)
DIG3: DS2.12 (D1), U3.7 (DIG_3)
DIG4: DS1.6 (D4), U3.3 (DIG_4)
DIG5: DS1.8 (D3), U3.10 (DIG_5)
DIG6: DS1.9 (D2), U3.5 (DIG_6)
DIG7: DS1.12 (D1), U3.8 (DIG_7)
DIN: U1.18 (AN1/RA1), U3.1 (DIN)
GND: BT1.2 (-), C1.2, C2.2, C4.2, C6.2, C12.2, C14.2, C15.2, C16.2, C17.2, C18.2, C19.2, C20.2, C22.2, LS1.2, MK1.2 (+), Q2.1 (E), R2.2, R7.2, R9.2, R10.2, R17.2, RV1.3, SW2.2 (B), SW3.2 (B), SW5.2, U1.5 (VSS), U2.5 (INH), U2.6 (PWDN), U2.9 (VSS), U3.4 (GND), U3.9 (GND), U4.4 (V-), U5.2 (-), U5.4 (GND), U6.1 (GND)
ISET: R26.1, U3.18 (ISET)
LEDA: D2.2 (A), R11.2
LEDC: D2.1 (K), Q1.3 (C)
LMBYP: C20.1, U5.7 (BYPASS)
LOAD: U1.2 (CMP1/AN3/RA3), U3.12 (LOAD)
MCLR: R1.2, SW5.1, U1.4 (~MCLR/Vpp/RA5)
MICAMP: C5.1, R5.1, U4.1
MICB: C3.1, MK1.1 (-), R3.2
MIC_AC1: C3.2, R4.1
MIC_AC2: C5.2, R12.1
MIC_INV: R4.2, R5.2, U4.2 (-)
M_EST: R25.1, U2.16 (ESt)
M_GS: R24.1, U2.3 (GS)
M_INN: R23.2, R24.2, U2.2 (IN-)
M_IN_AC: C11.2, R23.1
M_OSC1: U2.7 (OSC1), X1.1
M_OSC2: C13.1, U2.8 (OSC2), X1.2
M_Q1: U1.10 (RB4/PGM), U2.11 (Q1)
M_Q2: U1.11 (RB5), U2.12 (Q2)
M_Q3: U1.12 (RB6/T1OSC0/T1CKI/PGC), U2.13 (Q3)
M_Q4: U1.13 (RB7/T1OSI/PGD), U2.14 (Q4)
M_STD: U1.3 (TOCKI/CMP2/RA4), U2.15 (StD)
M_STGT: C12.1, R25.2, U2.17 (St/GT)
M_VREF: U2.1 (IN+), U2.4 (VRef)
OFFNORM: SW3.1 (A), U1.7 (RB1/RX/DT)
PD: C8.1, D1.2 (A), R17.1
PD_AC: C8.2, R18.1
PULSE: SW2.1 (A), U1.6 (RB0/INT)
Q2B: Q2.2 (B), R22.2
RXAMP: C9.1, C10.1, C11.1, R19.1, U4.7
RXINV: C9.2, R18.2, R19.2, U4.6 (-)
RX_AC: C10.2, Q2.3 (C), RV1.1
SEG_A: DS1.11 (A), DS2.11 (A), U3.14 (SEG_A)
SEG_B: DS1.7 (B), DS2.7 (B), U3.16 (SEG_B)
SEG_C: DS1.4 (C), DS2.4 (C), U3.20 (SEG_C)
SEG_D: DS1.2 (D), DS2.2 (D), U3.23 (SEG_D)
SEG_DP: DS1.3 (DP), DS2.3 (DP), U3.22 (SEG_DP)
SEG_E: DS1.1 (E), DS2.1 (E), U3.21 (SEG_E)
SEG_F: DS1.10 (F), DS2.10 (F), U3.15 (SEG_F)
SEG_G: DS1.5 (G), DS2.5 (G), U3.17 (SEG_G)
SPKC: C21.2, LS1.1
SPKO: C21.1, R27.1, U5.5
TALK_H: R2.1, R3.1, R8.1, R22.1, SW4.2, U1.17 (AN0/RA0)
TONE: C6.1, C7.1, R13.2, R14.2
TONEA: R13.1, U1.8 (RB2/TX/CK)
TONEB: R14.1, U1.9 (RB3/CCP1)
TONE_AC: C7.2, R15.1, R16.1
TXB: Q1.2 (B), R8.2, R9.1, R12.2, R15.2
TXE: Q1.1 (E), R10.1
VBAT: C1.1, SW1.1 (A), U6.2 (VIN)
VBAT_RAW: BT1.1 (+), SW1.2 (B)
VMID: C4.1, R6.2, R7.1, U4.3 (+), U4.5 (+)
ZOB: C22.1, R27.2

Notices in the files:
README.md:
Game-Maker 3.0's DOS menus, rebuilt from its source and running in the browser: the red and blue menu bar, with the Map Maker's menu open (By Gregory Stone, Copyright 1994) over Snowbound's disk
games/year2000/phone/README.md:
[ZEPPP](https://github.com/battlecoder/zeppp) ("Zero External Parts PIC Programmer", by battlecoder, MIT License) turns an Arduino Nano,
- ZEPPP (Zero External Parts PIC Programmer), battlecoder, MIT License: . The phone does not include or copy its code; the steps above only use it.
